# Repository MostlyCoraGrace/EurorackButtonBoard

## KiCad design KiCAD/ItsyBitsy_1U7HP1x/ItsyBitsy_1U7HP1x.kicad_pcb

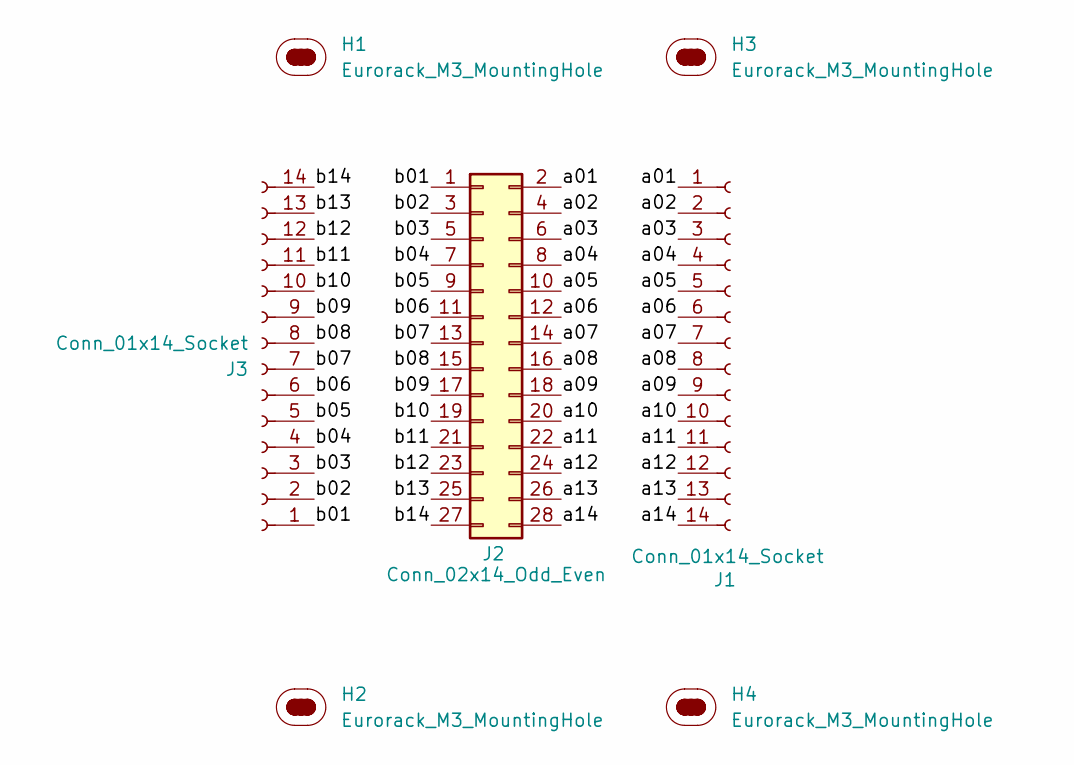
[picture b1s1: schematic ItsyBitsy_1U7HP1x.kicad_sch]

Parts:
H1, H2, H3, H4: Eurorack_M3_MountingHole; MountingHole_3.2mm_M3
J1, J3: Conn_01x14_Socket; PinSocket_1x14_P2.54mm_Vertical
J2: Conn_02x14_Odd_Even; PinHeader_2x14_P2.54mm_Horizontal

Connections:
/a01: J1.1, J2.2
/a02: J1.2, J2.4
/a03: J1.3, J2.6
/a04: J1.4, J2.8
/a05: J1.5, J2.10
/a06: J1.6, J2.12
/a07: J1.7, J2.14
/a08: J1.8, J2.16
/a09: J1.9, J2.18
/a10: J1.10, J2.20
/a11: J1.11, J2.22
/a12: J1.12, J2.24
/a13: J1.13, J2.26
/a14: J1.14, J2.28
/b01: J2.1, J3.1
/b02: J2.3, J3.2
/b03: J2.5, J3.3
/b04: J2.7, J3.4
/b05: J2.9, J3.5
/b06: J2.11, J3.6
/b07: J2.13, J3.7
/b08: J2.15, J3.8
/b09: J2.17, J3.9
/b10: J2.19, J3.10
/b11: J2.21, J3.11
/b12: J2.23, J3.12
/b13: J2.25, J3.13
/b14: J2.27, J3.14

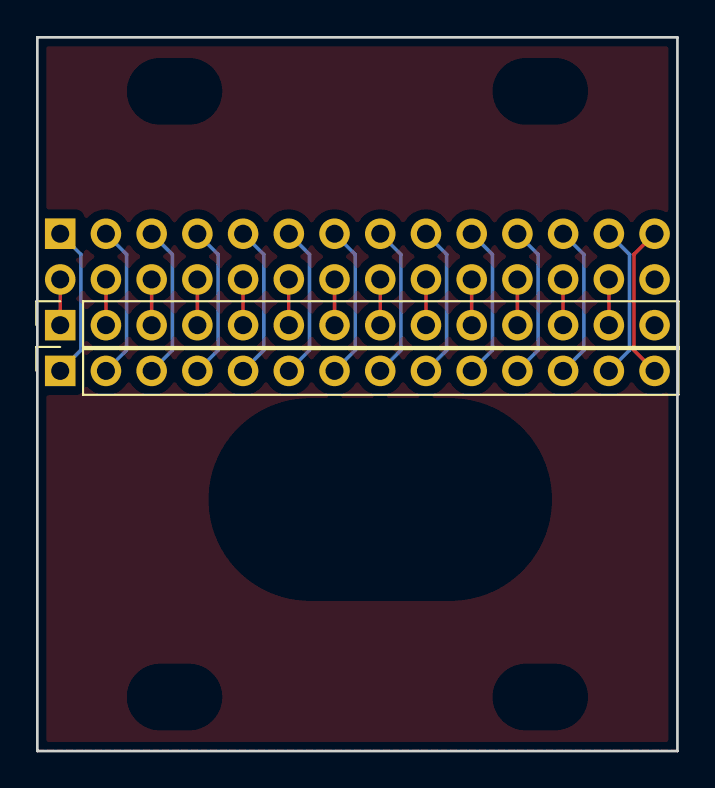
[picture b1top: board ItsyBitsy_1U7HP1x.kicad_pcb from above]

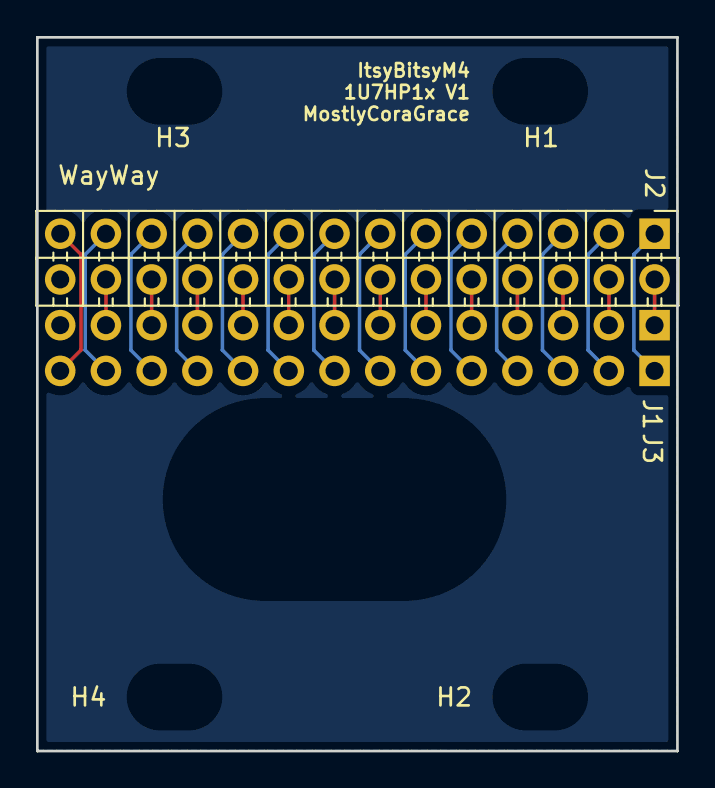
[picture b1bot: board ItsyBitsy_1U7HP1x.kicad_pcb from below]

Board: 2 copper layers, 35.6 x 39.7 mm, 7 parts (5 on the bottom side), 28 nets.

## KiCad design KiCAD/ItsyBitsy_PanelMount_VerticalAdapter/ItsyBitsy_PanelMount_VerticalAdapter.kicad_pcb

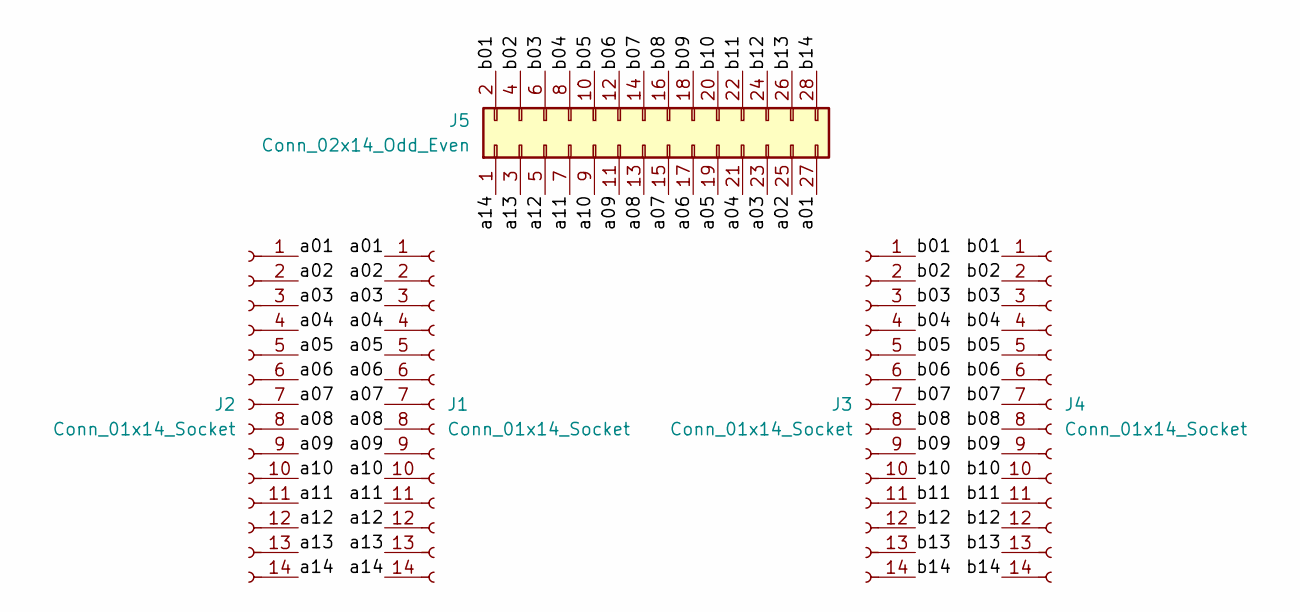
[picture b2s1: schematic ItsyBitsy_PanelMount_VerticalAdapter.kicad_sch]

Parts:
J1, J2, J3, J4: Conn_01x14_Socket; PinSocket_1x14_P2.54mm_Vertical
J5: Conn_02x14_Odd_Even; PinHeader_2x14_P2.54mm_Horizontal

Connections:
/a01: J1.1, J2.1, J5.27
/a02: J1.2, J2.2, J5.25
/a03: J1.3, J2.3, J5.23
/a04: J1.4, J2.4, J5.21
/a05: J1.5, J2.5, J5.19
/a06: J1.6, J2.6, J5.17
/a07: J1.7, J2.7, J5.15
/a08: J1.8, J2.8, J5.13
/a09: J1.9, J2.9, J5.11
/a10: J1.10, J2.10, J5.9
/a11: J1.11, J2.11, J5.7
/a12: J1.12, J2.12, J5.5
/a13: J1.13, J2.13, J5.3
/a14: J1.14, J2.14, J5.1
/b01: J3.1, J4.1, J5.2
/b02: J3.2, J4.2, J5.4
/b03: J3.3, J4.3, J5.6
/b04: J3.4, J4.4, J5.8
/b05: J3.5, J4.5, J5.10
/b06: J3.6, J4.6, J5.12
/b07: J3.7, J4.7, J5.14
/b08: J3.8, J4.8, J5.16
/b09: J3.9, J4.9, J5.18
/b10: J3.10, J4.10, J5.20
/b11: J3.11, J4.11, J5.22
/b12: J3.12, J4.12, J5.24
/b13: J3.13, J4.13, J5.26
/b14: J3.14, J4.14, J5.28

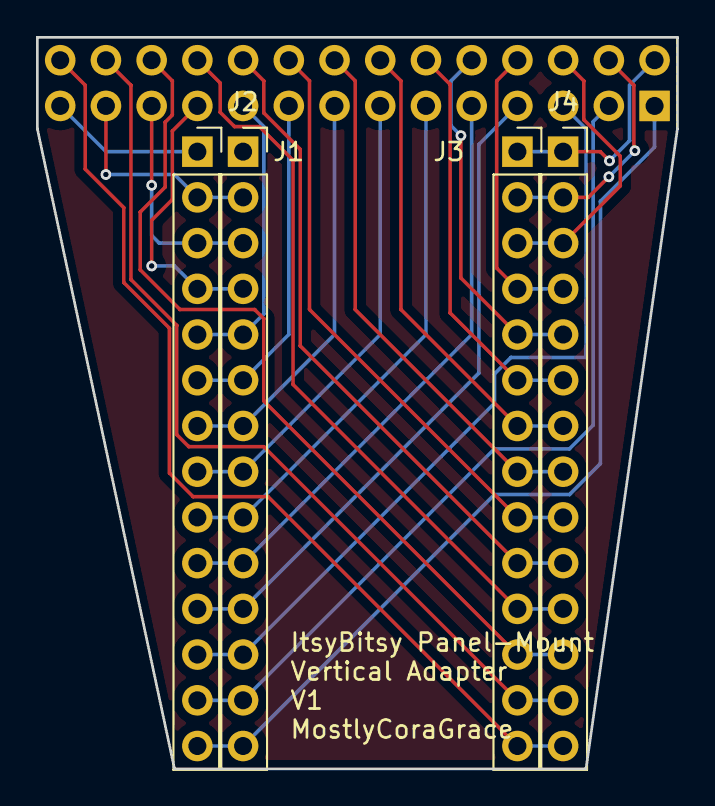
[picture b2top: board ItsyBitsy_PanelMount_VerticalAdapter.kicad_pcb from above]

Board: 2 copper layers, 35.6 x 40.6 mm, 5 parts (1 on the bottom side), 28 nets.
